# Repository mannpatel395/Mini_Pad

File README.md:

# Mini_Pad

# Discription

This custom buit micropad is powered by a Seeed Studio XIAO RP2040 and runs QMK firmware to function as a dedicated video and photo editing controller.
It has 4 mechanical switchers and a rotary encoder including 0.91 oled display. They are programmed to do various tasks like tool selection, layer toggling and intutive timeline scrubbing.
Oled display is used to show the active layer and current keybinds while LED attached changes color as per different operational modes selected.

# PCB

This is custom made PCB for Mini_Pad

Schematic

PCB Layout

# CAD 

This is custom CAD model to enclose whole PCB and give sleek look

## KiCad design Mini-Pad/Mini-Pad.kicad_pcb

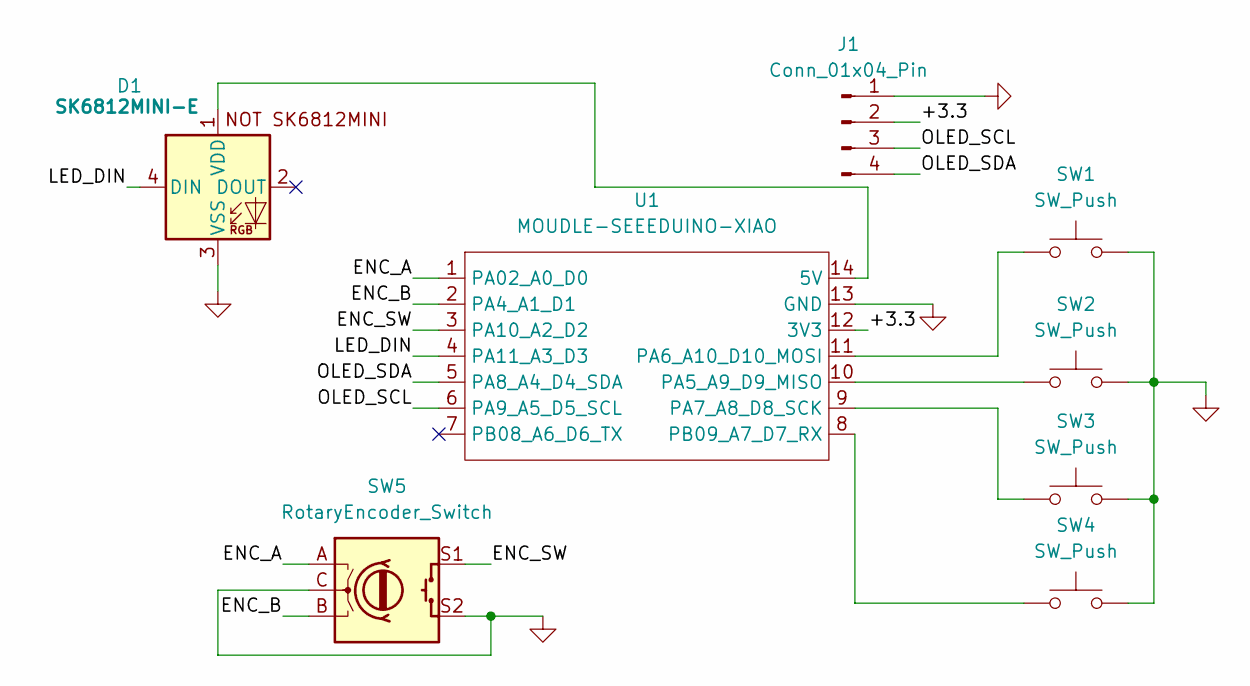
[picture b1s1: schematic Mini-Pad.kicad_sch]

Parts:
D1: SK6812MINI-E; SK6812MINI-E_fixed
J1: Conn_01x04_Pin; SSD1306-0.91-OLED-4pin-128x32
SW1, SW2, SW3, SW4: SW_Push; SW_Cherry_MX_1.00u_PCB
SW5: RotaryEncoder_Switch; RotaryEncoder_Alps_EC11E-Switch_Vertical_H20mm
U1: MOUDLE-SEEEDUINO-XIAO; XIAO-Generic-Hybrid-14P-2.54-21X17.8MM

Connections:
/+3.3: J1.2, U1.12 (3V3)
/ENC_A: SW5.A, U1.1 (PA02_A0_D0)
/ENC_B: SW5.B, U1.2 (PA4_A1_D1)
/ENC_SW: SW5.S1, U1.3 (PA10_A2_D2)
/LED_DIN: D1.4 (DIN), U1.4 (PA11_A3_D3)
/OLED_SCL: J1.3, U1.6 (PA9_A5_D5_SCL)
/OLED_SDA: J1.4, U1.5 (PA8_A4_D4_SDA)
GND: D1.3 (VSS), J1.1, SW1.2, SW2.2, SW3.2, SW4.2, SW5.C, SW5.S2, U1.13 (GND)
unnamed: D1.1 (VDD), U1.14 (5V)
unnamed: SW2.1, U1.10 (PA5_A9_D9_MISO)
unnamed: SW1.1, U1.11 (PA6_A10_D10_MOSI)
unnamed: SW3.1, U1.9 (PA7_A8_D8_SCK)
unnamed: SW4.1, U1.8 (PB09_A7_D7_RX)

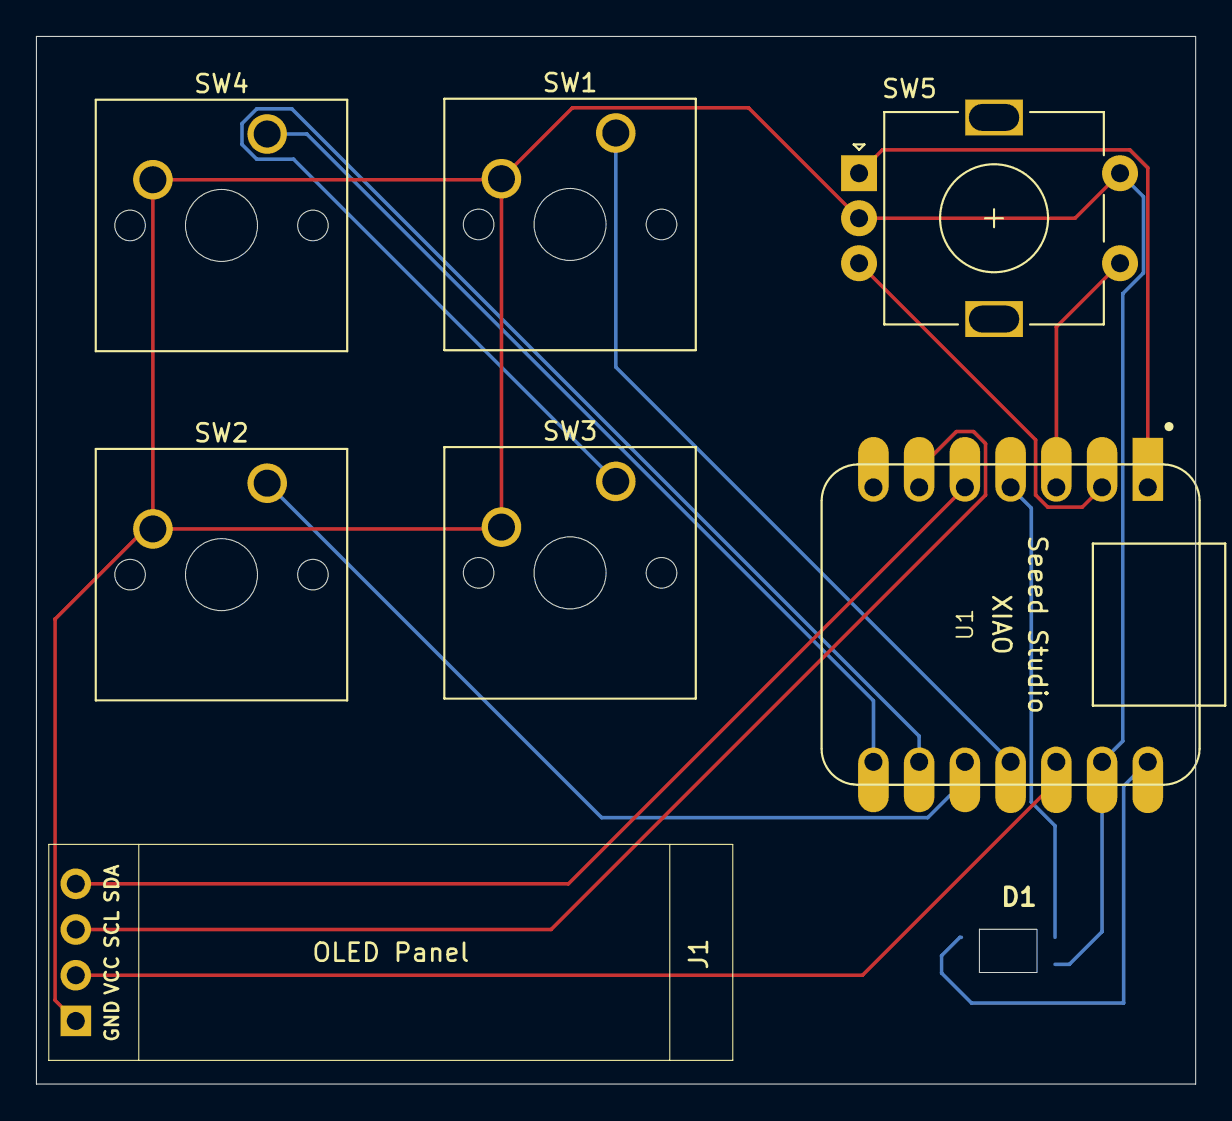
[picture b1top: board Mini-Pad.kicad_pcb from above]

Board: 2 copper layers, 64.4 x 58.2 mm, 8 parts (0 on the bottom side), 13 nets.
